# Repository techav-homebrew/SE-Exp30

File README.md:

# SE-Exp30 Mac SE Accelerator
Minimal 68030 &amp; 68882 accelerator card for the Macintosh SE

This project is not intended to be the fastest or most feature-rich accelerator for the Mac SE. Its primary goal is to be simple and transparent to Mac OS. Without the FPU, it should be able to function as just a faster Mac SE. To make full use of the FPU and the 68030's onboard cache, MacOS may need an init or extension to enable these features and advertise their presence to applications. 

The glue logic is entirely contained in a single 64-macrocel CPLD. Either an Altera EPM7064 or an Atmel ATF1504 will work. It is programmed and compiled for the Altera chip, but tested with the Atmel chip, using the free POF2JED software to convert the compiled configuration to the Atmel format. 

Should the initial design prove successful, future revisions may add cache or RAM on a 32-bit bus to further accelerate the SE. 

## Bill of Materials
Parts count is minimal
- Motorola 68030 CPU (MC68030RC or MC68030RP)
- Motorola 68882 FPU (MC68882RC)
- Microchip/Atmel ATF1504AS-10JU84 (PLLC-84)
- 7x 74'245 buffers (SOIC-20)
- 2x 10uF Electrolyic capacitors (5mm, 2.5mm lead spacing)
- 33x 1uF Ceramic capacitors (0805)
- 16x 4k7 resistors (0805)
- TTL Crystal Oscillator (DIP-8)
- DIN 41612-C 96-pin right-angle connector (male)
- optional 4-pin floppy/Berg power connector

None of the part values are especially critical. The oscillator frequency should match the intended CPU/FPU speed, and the speed grade for the CPLD should be appropriate for the target speed as well. Timing for the CPLD was planned with a 10ns CPLD and 50MHz CPU in mind. As the 68030 CPU and 68882 FPU are no longer produced, it is left to the reader to source these parts and determine the appropriate oscillator frequency to use with whatever parts are available. Processors were originally offered in 16MHz, 20MHz, 25MHz, 33MHz, 40MHz, and 50MHz ratings. It may be necessary to convert the PCB to 4-layers and insert internal power/ground planes to achieve higher clock rates. 

All capacitors on the BOM are included for bypass/filter purposes, so their values are not critical. Lower capacitance isn't recommended, but higher values may certainly be substituted. Similarly, the resistors only serve as pull-ups so their values are also not critical. 

## Power Supply
The Mac SE is rated to provide 7.5W on the 5V rail for PDS cards. This card may exceed that 7.5W rating. Depending on the configuration of the SE model (e.g. presence of a hard drive) and the health of the power supply, a separate 5V power supply may be necessary to power this accelerator. A footprint is provided for a 4-pin floppy (Berg) connector. If an external power supply is used, the jumpers J1, J2, J3 should be left open. If the card will be powered via the PDS slot, these jumpers should be closed, and nothing should be connected to the power connector.

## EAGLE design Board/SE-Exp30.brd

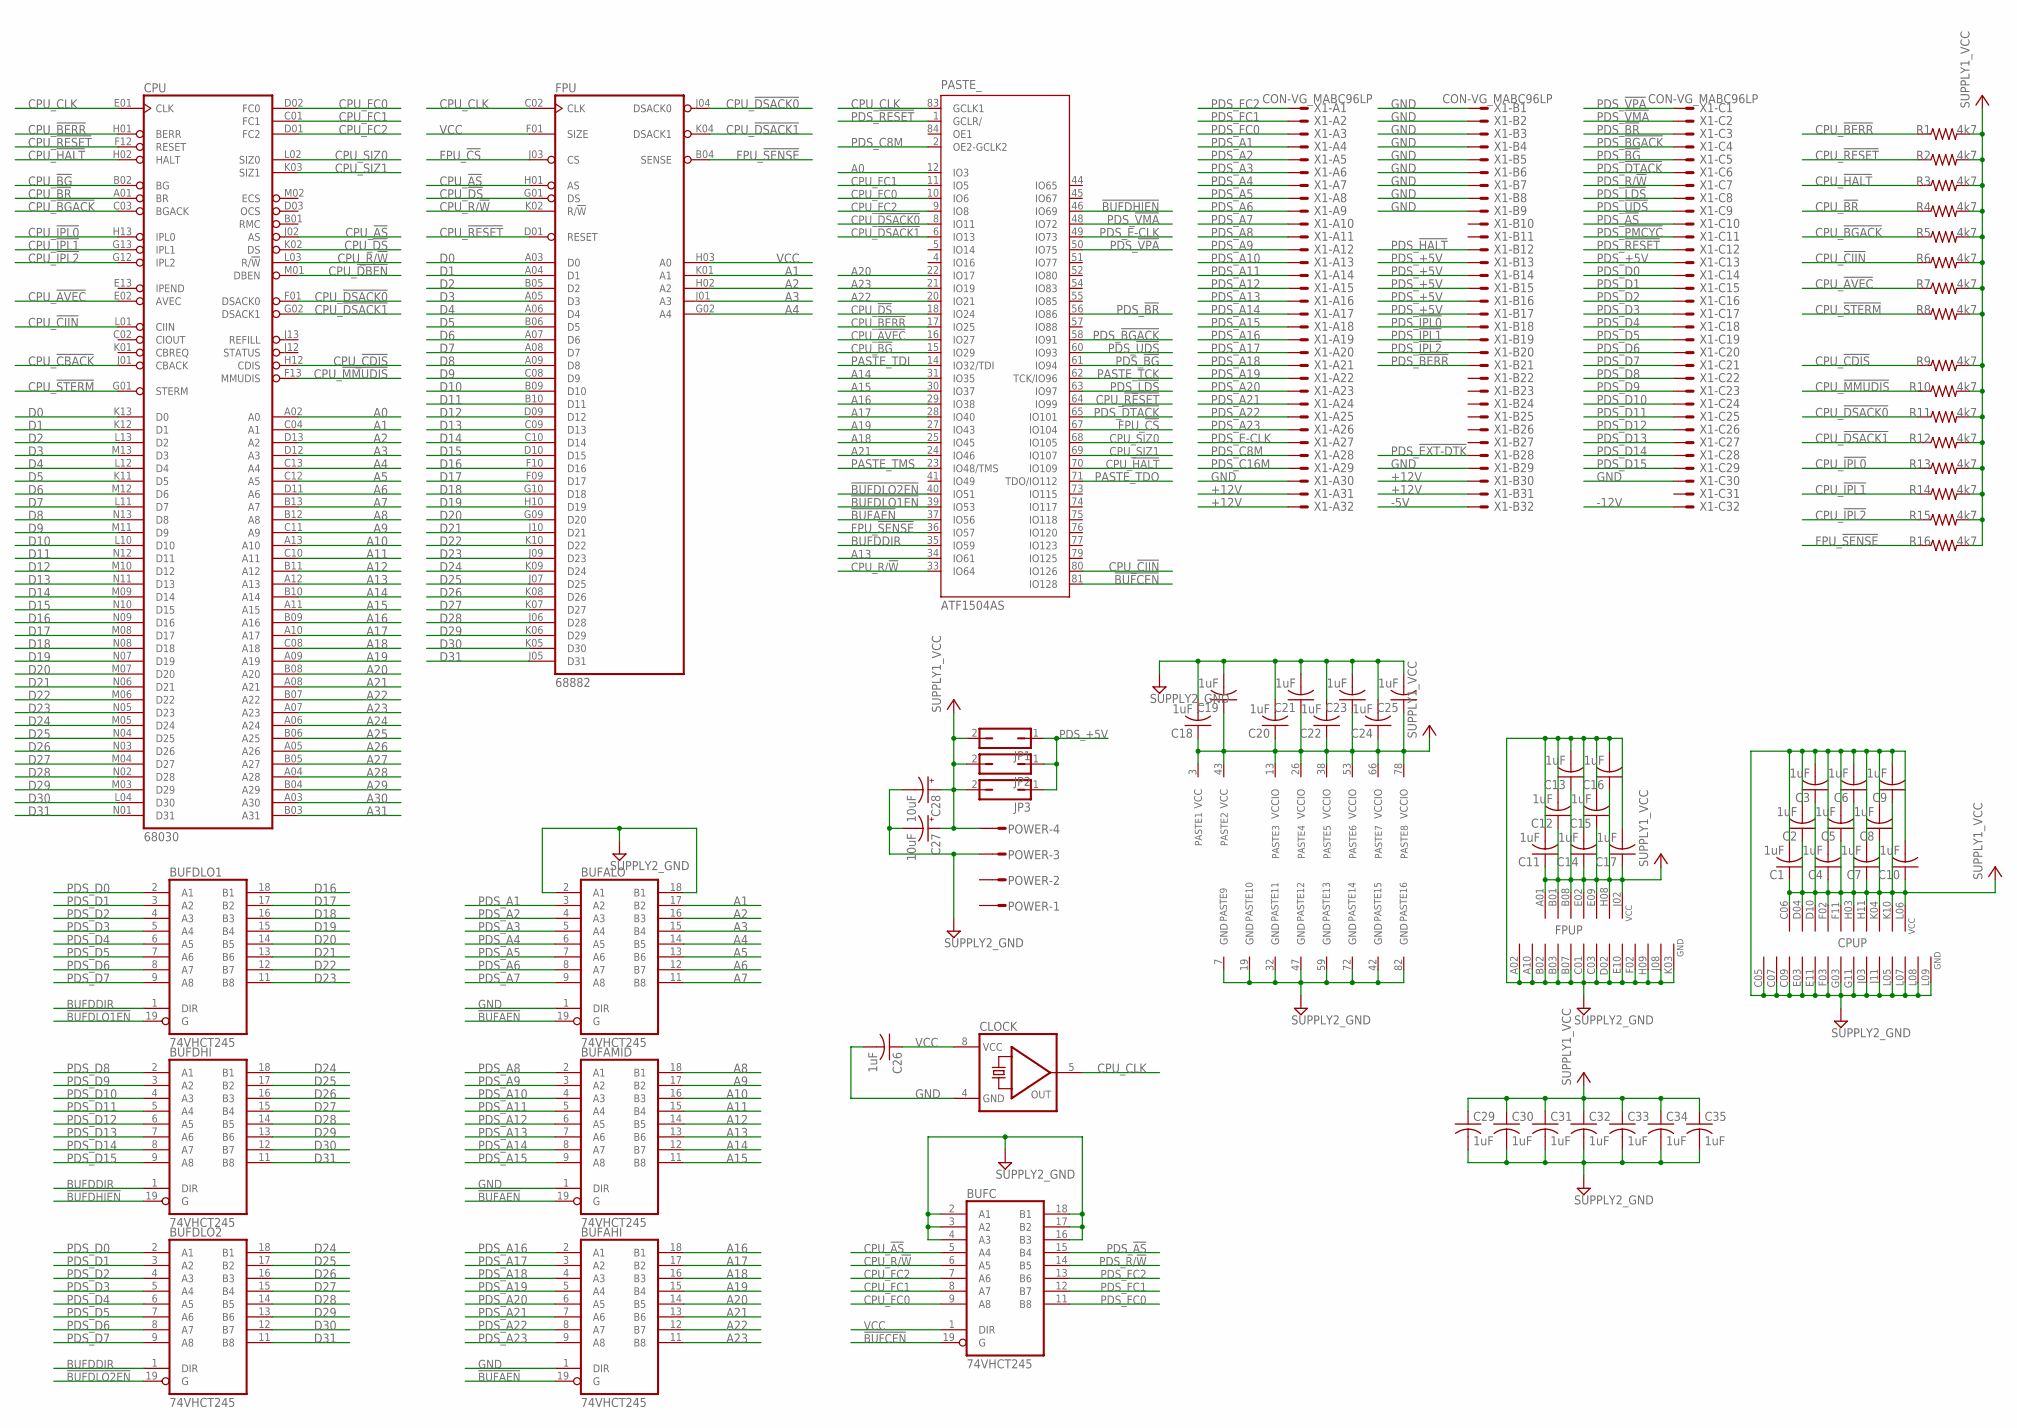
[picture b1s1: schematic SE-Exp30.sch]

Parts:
BUFAHI: 74VHCT245; 74XX-US_SO20W
BUFALO: 74VHCT245; 74XX-US_SO20W
BUFAMID: 74VHCT245; 74XX-US_SO20W
BUFC: 74VHCT245; 74XX-US_SO20W
BUFDHI: 74VHCT245; 74XX-US_SO20W
BUFDLO1, BUFDLO2: 74VHCT245; 74XX-US_SO20W
C1, C2, C3, C4, C5, C6, C7, C8, C9, C10, C11, C12, C13, C14, C15, C16, C17, C18, C19, C20, C21, C22, C23, C24, C25, C26, C29, C30, C31, C32, C33, C34, C35: 1uF; RCL_C0805
C27, C28: 10uF; RCL_E2,5-5
CLOCK: CRYSTAL_QG5460; CRYSTAL_DIL08S
CPU: 68030; MICRO-MC68000_MPGA128
FPU: 68882; MICRO-MC68000_MPGA68
JP1, JP2, JP3: JUMPER_JP1Q; JUMPER_JP1
PASTE: ATF1504AS; SE-EXP30_S84
POWER: CON-AMP-MT_L04P
R1, R2, R3, R4, R5, R6, R7, R8, R9, R10, R11, R12, R13, R14, R15, R16: 4k7; RCL_R0805
X1: CON-VG_MABC96LP

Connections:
!BUFAEN: BUFAHI.19 (G), BUFALO.19 (G), BUFAMID.19 (G), PASTE.37 (IO56)
!BUFCEN: BUFC.19 (G), PASTE.81 (IO128)
!BUFDHIEN: BUFDHI.19 (G), PASTE.46 (IO69)
!BUFDLO1EN: BUFDLO1.19 (G), PASTE.39 (IO53)
!BUFDLO2EN: BUFDLO2.19 (G), PASTE.40 (IO51)
+12V: X1.A31, X1.A32, X1.B30, X1.B31
-5V: X1.B32
-12V: X1.C32
A0: CPU.A02 (A0), PASTE.12 (IO3)
A1: BUFALO.17 (B2), CPU.C04 (A1), FPU.K01 (A1)
A2: BUFALO.16 (B3), CPU.D13 (A2), FPU.H02 (A2)
A3: BUFALO.15 (B4), CPU.D12 (A3), FPU.J01 (A3)
A4: BUFALO.14 (B5), CPU.C13 (A4), FPU.G02 (A4)
A5: BUFALO.13 (B6), CPU.C12 (A5)
A6: BUFALO.12 (B7), CPU.D11 (A6)
A7: BUFALO.11 (B8), CPU.B13 (A7)
A8: BUFAMID.18 (B1), CPU.B12 (A8)
A9: BUFAMID.17 (B2), CPU.C11 (A9)
A10: BUFAMID.16 (B3), CPU.A13 (A10)
A11: BUFAMID.15 (B4), CPU.C10 (A11)
A12: BUFAMID.14 (B5), CPU.B11 (A12)
A13: BUFAMID.13 (B6), CPU.A12 (A13), PASTE.34 (IO61)
A14: BUFAMID.12 (B7), CPU.B10 (A14), PASTE.31 (IO35)
A15: BUFAMID.11 (B8), CPU.A11 (A15), PASTE.30 (IO37)
A16: BUFAHI.18 (B1), CPU.B09 (A16), PASTE.29 (IO38)
A17: BUFAHI.17 (B2), CPU.A10 (A17), PASTE.28 (IO40)
A18: BUFAHI.16 (B3), CPU.C08 (A18), PASTE.25 (IO45)
A19: BUFAHI.15 (B4), CPU.A09 (A19), PASTE.27 (IO43)
A20: BUFAHI.14 (B5), CPU.B08 (A20), PASTE.22 (IO17)
A21: BUFAHI.13 (B6), CPU.A08 (A21), PASTE.24 (IO46)
A22: BUFAHI.12 (B7), CPU.B07 (A22), PASTE.20 (IO21)
A23: BUFAHI.11 (B8), CPU.A07 (A23), PASTE.21 (IO19)
A24: CPU.A06 (A24)
A25: CPU.B06 (A25)
A26: CPU.A05 (A26)
A27: CPU.B05 (A27)
A28: CPU.A04 (A28)
A29: CPU.B04 (A29)
A30: CPU.A03 (A30)
A31: CPU.B03 (A31)
BUFDDIR: BUFDHI.1 (DIR), BUFDLO1.1 (DIR), BUFDLO2.1 (DIR), PASTE.35 (IO59)
CPU_!AS: BUFC.5 (A4), CPU.J02 (AS), FPU.H01 (AS)
CPU_!AVEC: CPU.E02 (AVEC), PASTE.16 (IO27), R7.1
CPU_!BERR: CPU.H01 (BERR), PASTE.17 (IO25), R1.1
CPU_!BG: CPU.B02 (BG), PASTE.15 (IO29)
CPU_!BGACK: CPU.C03 (BGACK), R5.1
CPU_!BR: CPU.A01 (BR), R4.1
CPU_!CBACK: CPU.J01 (CBACK)
CPU_!CDIS: CPU.H12 (CDIS), R9.1
CPU_!CIIN: CPU.L01 (CIIN), PASTE.80 (IO126), R6.1
CPU_!DBEN: CPU.M01 (DBEN)
CPU_!DS: CPU.K02 (DS), FPU.G01 (DS), PASTE.18 (IO24)
CPU_!DSACK0: CPU.F01 (DSACK0), FPU.J04 (DSACK0), PASTE.8 (IO11), R11.1
CPU_!DSACK1: CPU.G02 (DSACK1), FPU.K04 (DSACK1), PASTE.6 (IO13), R12.1
CPU_!HALT: CPU.H02 (HALT), PASTE.70 (IO109), R3.1
CPU_!IPL0: CPU.H13 (IPL0), R13.1
CPU_!IPL1: CPU.G13 (IPL1), R14.1
CPU_!IPL2: CPU.G12 (IPL2), R15.1
CPU_!MMUDIS: CPU.F13 (MMUDIS), R10.1
CPU_!RESET: CPU.F12 (RESET), FPU.D01 (RESET), PASTE.64 (IO99), R2.1
CPU_!STERM: CPU.G01 (STERM), R8.1
CPU_CLK: CLOCK.5 (OUT), CPU.E01 (CLK), FPU.C02 (CLK), PASTE.83 (GCLK1)
CPU_FC0: BUFC.9 (A8), CPU.D02 (FC0), PASTE.10 (IO6)
CPU_FC1: BUFC.8 (A7), CPU.C01 (FC1), PASTE.11 (IO5)
CPU_FC2: BUFC.7 (A6), CPU.D01 (FC2), PASTE.9 (IO8)
CPU_R/!W: BUFC.6 (A5), CPU.L03 (R/!W), FPU.K02 (R/!W), PASTE.33 (IO64)
CPU_SIZ0: CPU.L02 (SIZ0), PASTE.68 (IO105)
CPU_SIZ1: CPU.K03 (SIZ1), PASTE.69 (IO107)
D0: CPU.K13 (D0), FPU.A03 (D0)
D1: CPU.K12 (D1), FPU.A04 (D1)
D2: CPU.L13 (D2), FPU.B05 (D2)
D3: CPU.M13 (D3), FPU.A05 (D3)
D4: CPU.L12 (D4), FPU.A06 (D4)
D5: CPU.K11 (D5), FPU.B06 (D5)
D6: CPU.M12 (D6), FPU.A07 (D6)
D7: CPU.L11 (D7), FPU.A08 (D7)
D8: CPU.N13 (D8), FPU.A09 (D8)
D9: CPU.M11 (D9), FPU.C08 (D9)
D10: CPU.L10 (D10), FPU.B09 (D10)
D11: CPU.N12 (D11), FPU.B10 (D11)
D12: CPU.M10 (D12), FPU.D09 (D12)
D13: CPU.N11 (D13), FPU.C09 (D13)
D14: CPU.M09 (D14), FPU.C10 (D14)
D15: CPU.N10 (D15), FPU.D10 (D15)
D16: BUFDLO1.18 (B1), CPU.N09 (D16), FPU.F10 (D16)
D17: BUFDLO1.17 (B2), CPU.M08 (D17), FPU.F09 (D17)
D18: BUFDLO1.16 (B3), CPU.N08 (D18), FPU.G10 (D18)
D19: BUFDLO1.15 (B4), CPU.N07 (D19), FPU.H10 (D19)
D20: BUFDLO1.14 (B5), CPU.M07 (D20), FPU.G09 (D20)
D21: BUFDLO1.13 (B6), CPU.N06 (D21), FPU.J10 (D21)
D22: BUFDLO1.12 (B7), CPU.M06 (D22), FPU.K10 (D22)
D23: BUFDLO1.11 (B8), CPU.N05 (D23), FPU.J09 (D23)
D24: BUFDHI.18 (B1), BUFDLO2.18 (B1), CPU.M05 (D24), FPU.K09 (D24)
D25: BUFDHI.17 (B2), BUFDLO2.17 (B2), CPU.N04 (D25), FPU.J07 (D25)
D26: BUFDHI.16 (B3), BUFDLO2.16 (B3), CPU.N03 (D26), FPU.K08 (D26)
D27: BUFDHI.15 (B4), BUFDLO2.15 (B4), CPU.M04 (D27), FPU.K07 (D27)
D28: BUFDHI.14 (B5), BUFDLO2.14 (B5), CPU.N02 (D28), FPU.J06 (D28)
D29: BUFDHI.13 (B6), BUFDLO2.13 (B6), CPU.M03 (D29), FPU.K06 (D29)
D30: BUFDHI.12 (B7), BUFDLO2.12 (B7), CPU.L04 (D30), FPU.K05 (D30)
D31: BUFDHI.11 (B8), BUFDLO2.11 (B8), CPU.N01 (D31), FPU.J05 (D31)
FPU_!CS: FPU.J03 (CS), PASTE.67 (IO104)
FPU_!SENSE: FPU.B04 (SENSE), PASTE.36 (IO57), R16.1
GND: BUFAHI.1 (DIR), BUFAHI.10 (GND), BUFALO.1 (DIR), BUFALO.2 (A1), BUFALO.10 (GND), BUFALO.18 (B1), BUFAMID.1 (DIR), BUFAMID.10 (GND), BUFC.2 (A1), BUFC.3 (A2), BUFC.4 (A3), BUFC.10 (GND), BUFC.16 (B3), BUFC.17 (B2), BUFC.18 (B1), BUFDHI.10 (GND), BUFDLO1.10 (GND), BUFDLO2.10 (GND), C1.2, C2.2, C3.2, C4.2, C5.2, C6.2, C7.2, C8.2, C9.2, C10.2, C11.2, C12.2, C13.2, C14.2, C15.2, C16.2, C17.2, C18.2, C19.2, C20.2, C21.2, C22.2, C23.2, C24.2, C25.2, C26.2, C27.-, C28.-, C29.2, C30.2, C31.2, C32.2, C33.2, C34.2, C35.2, CLOCK.4 (GND), CPU.C05 (GND), CPU.C07 (GND), CPU.C09 (GND), CPU.E03 (GND), CPU.E11 (GND), CPU.F03 (GND), CPU.G03 (GND), CPU.G11 (GND), CPU.J03 (GND), CPU.J11 (GND), CPU.L05 (GND), CPU.L07 (GND), CPU.L08 (GND), CPU.L09 (GND), FPU.A02 (GND), FPU.A10 (GND), FPU.B02 (GND), FPU.B03 (GND), FPU.B07 (GND), FPU.C01 (GND), FPU.C03 (GND), FPU.D02 (GND), FPU.E10 (GND), FPU.F02 (GND), FPU.H09 (GND), FPU.J08 (GND), FPU.K03 (GND), PASTE.7 (GND), PASTE.19 (GND), PASTE.32 (GND), PASTE.42 (GND), PASTE.47 (GND), PASTE.59 (GND), PASTE.72 (GND), PASTE.82 (GND), POWER.3, X1.A30, X1.B1, X1.B2, X1.B3, X1.B4, X1.B5, X1.B6, X1.B7, X1.B8, X1.B9, X1.B29, X1.C30
PASTE_TCK: PASTE.62 (TCK/IO96)
PASTE_TDI: PASTE.14 (IO32/TDI)
PASTE_TDO: PASTE.71 (TDO/IO112)
PASTE_TMS: PASTE.23 (IO48/TMS)
PDS_!AS: BUFC.15 (B4), X1.C10
PDS_!BERR: X1.B21
PDS_!BG: PASTE.61 (IO94), X1.C5
PDS_!BGACK: PASTE.58 (IO91), X1.C4
PDS_!BR: PASTE.56 (IO86), X1.C3
PDS_!DTACK: PASTE.65 (IO101), X1.C6
PDS_!EXT-DTK: X1.B28
PDS_!HALT: X1.B12
PDS_!IPL0: X1.B18
PDS_!IPL1: X1.B19
PDS_!IPL2: X1.B20
PDS_!LDS: PASTE.63 (IO97), X1.C8
PDS_!PMCYC: X1.C11
PDS_!RESET: PASTE.1 (GCLR/), X1.C12
PDS_!UDS: PASTE.60 (IO93), X1.C9
PDS_!VMA: PASTE.48 (IO72), X1.C2
PDS_!VPA: PASTE.50 (IO75), X1.C1
PDS_+5V: JP1.1, JP2.1, JP3.1, X1.B13, X1.B14, X1.B15, X1.B16, X1.B17, X1.C13
PDS_A1: BUFALO.3 (A2), X1.A4
PDS_A2: BUFALO.4 (A3), X1.A5
PDS_A3: BUFALO.5 (A4), X1.A6
PDS_A4: BUFALO.6 (A5), X1.A7
PDS_A5: BUFALO.7 (A6), X1.A8
PDS_A6: BUFALO.8 (A7), X1.A9
PDS_A7: BUFALO.9 (A8), X1.A10
PDS_A8: BUFAMID.2 (A1), X1.A11
PDS_A9: BUFAMID.3 (A2), X1.A12
PDS_A10: BUFAMID.4 (A3), X1.A13
PDS_A11: BUFAMID.5 (A4), X1.A14
PDS_A12: BUFAMID.6 (A5), X1.A15
PDS_A13: BUFAMID.7 (A6), X1.A16
PDS_A14: BUFAMID.8 (A7), X1.A17
PDS_A15: BUFAMID.9 (A8), X1.A18
PDS_A16: BUFAHI.2 (A1), X1.A19
PDS_A17: BUFAHI.3 (A2), X1.A20
PDS_A18: BUFAHI.4 (A3), X1.A21
PDS_A19: BUFAHI.5 (A4), X1.A22
PDS_A20: BUFAHI.6 (A5), X1.A23
PDS_A21: BUFAHI.7 (A6), X1.A24
PDS_A22: BUFAHI.8 (A7), X1.A25
PDS_A23: BUFAHI.9 (A8), X1.A26
PDS_C8M: PASTE.2 (OE2-GCLK2), X1.A28
PDS_C16M: X1.A29
PDS_D0: BUFDLO1.2 (A1), BUFDLO2.2 (A1), X1.C14
PDS_D1: BUFDLO1.3 (A2), BUFDLO2.3 (A2), X1.C15
PDS_D2: BUFDLO1.4 (A3), BUFDLO2.4 (A3), X1.C16
PDS_D3: BUFDLO1.5 (A4), BUFDLO2.5 (A4), X1.C17
PDS_D4: BUFDLO1.6 (A5), BUFDLO2.6 (A5), X1.C18
PDS_D5: BUFDLO1.7 (A6), BUFDLO2.7 (A6), X1.C19
PDS_D6: BUFDLO1.8 (A7), BUFDLO2.8 (A7), X1.C20
PDS_D7: BUFDLO1.9 (A8), BUFDLO2.9 (A8), X1.C21
PDS_D8: BUFDHI.2 (A1), X1.C22
PDS_D9: BUFDHI.3 (A2), X1.C23
PDS_D10: BUFDHI.4 (A3), X1.C24
PDS_D11: BUFDHI.5 (A4), X1.C25
PDS_D12: BUFDHI.6 (A5), X1.C26
PDS_D13: BUFDHI.7 (A6), X1.C27
PDS_D14: BUFDHI.8 (A7), X1.C28
PDS_D15: BUFDHI.9 (A8), X1.C29
PDS_E-CLK: PASTE.49 (IO73), X1.A27
PDS_FC0: BUFC.11 (B8), X1.A3
PDS_FC1: BUFC.12 (B7), X1.A2
PDS_FC2: BUFC.13 (B6), X1.A1
PDS_R/!W: BUFC.14 (B5), X1.C7
VCC: BUFAHI.20 (VCC), BUFALO.20 (VCC), BUFAMID.20 (VCC), BUFC.1 (DIR), BUFC.20 (VCC), BUFDHI.20 (VCC), BUFDLO1.20 (VCC), BUFDLO2.20 (VCC), C1.1, C2.1, C3.1, C4.1, C5.1, C6.1, C7.1, C8.1, C9.1, C10.1, C11.1, C12.1, C13.1, C14.1, C15.1, C16.1, C17.1, C18.1, C19.1, C20.1, C21.1, C22.1, C23.1, C24.1, C25.1, C26.1, C27.+, C28.+, C29.1, C30.1, C31.1, C32.1, C33.1, C34.1, C35.1, CLOCK.8 (VCC), CPU.C06 (VCC), CPU.D04 (VCC), CPU.D10 (VCC), CPU.F02 (VCC), CPU.F11 (VCC), CPU.H03 (VCC), CPU.H11 (VCC), CPU.K04 (VCC), CPU.K10 (VCC), CPU.L06 (VCC), FPU.A01 (VCC), FPU.B01 (VCC), FPU.B08 (VCC), FPU.E02 (VCC), FPU.E09 (VCC), FPU.F01 (SIZE), FPU.H03 (A0), FPU.H08 (VCC), FPU.J02 (VCC), JP1.2, JP2.2, JP3.2, PASTE.3 (VCC), PASTE.13 (VCCIO), PASTE.26 (VCCIO), PASTE.38 (VCCIO), PASTE.43 (VCC), PASTE.53 (VCCIO), PASTE.66 (VCCIO), PASTE.78 (VCCIO), POWER.4, R1.2, R2.2, R3.2, R4.2, R5.2, R6.2, R7.2, R8.2, R9.2, R10.2, R11.2, R12.2, R13.2, R14.2, R15.2, R16.2

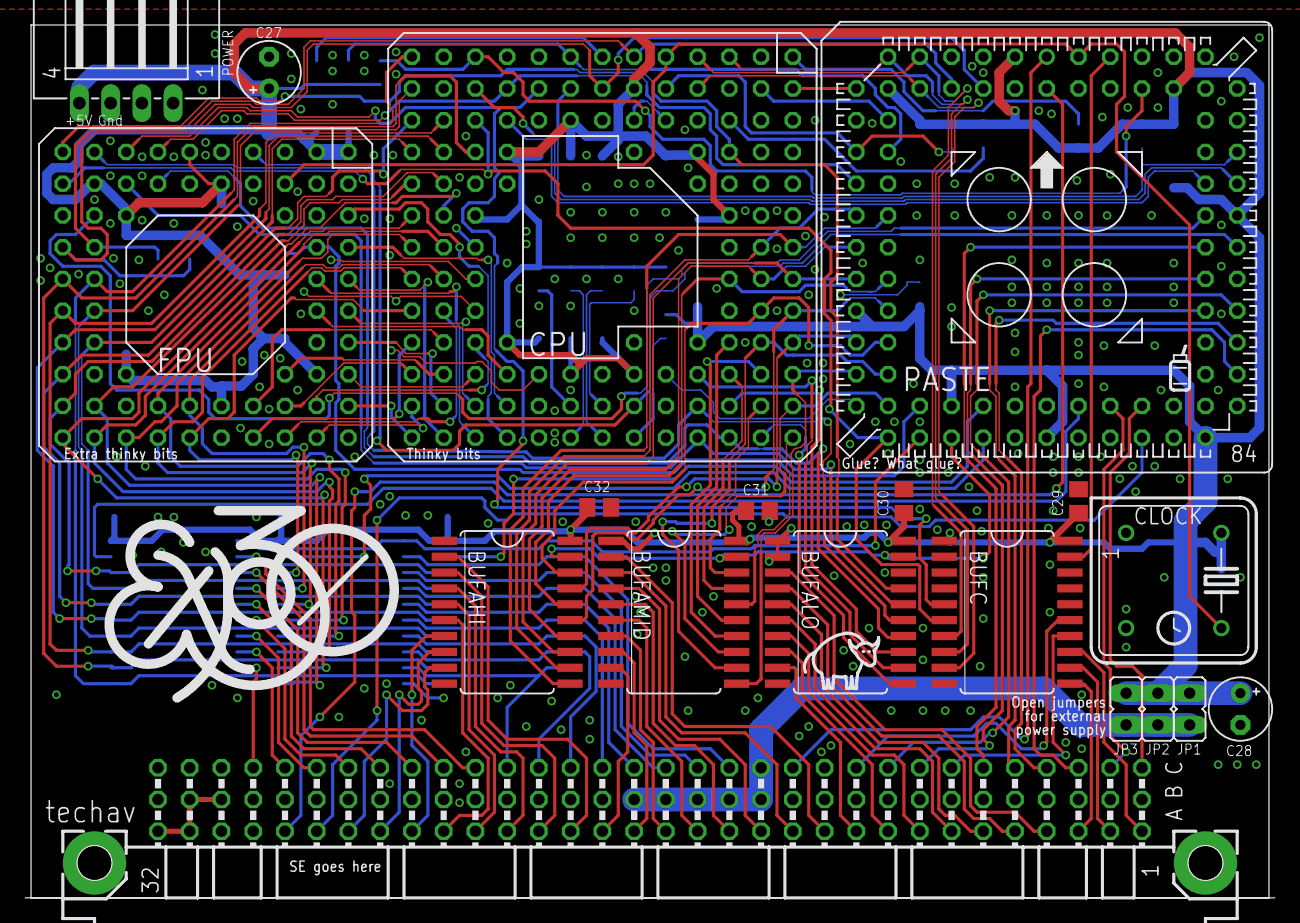
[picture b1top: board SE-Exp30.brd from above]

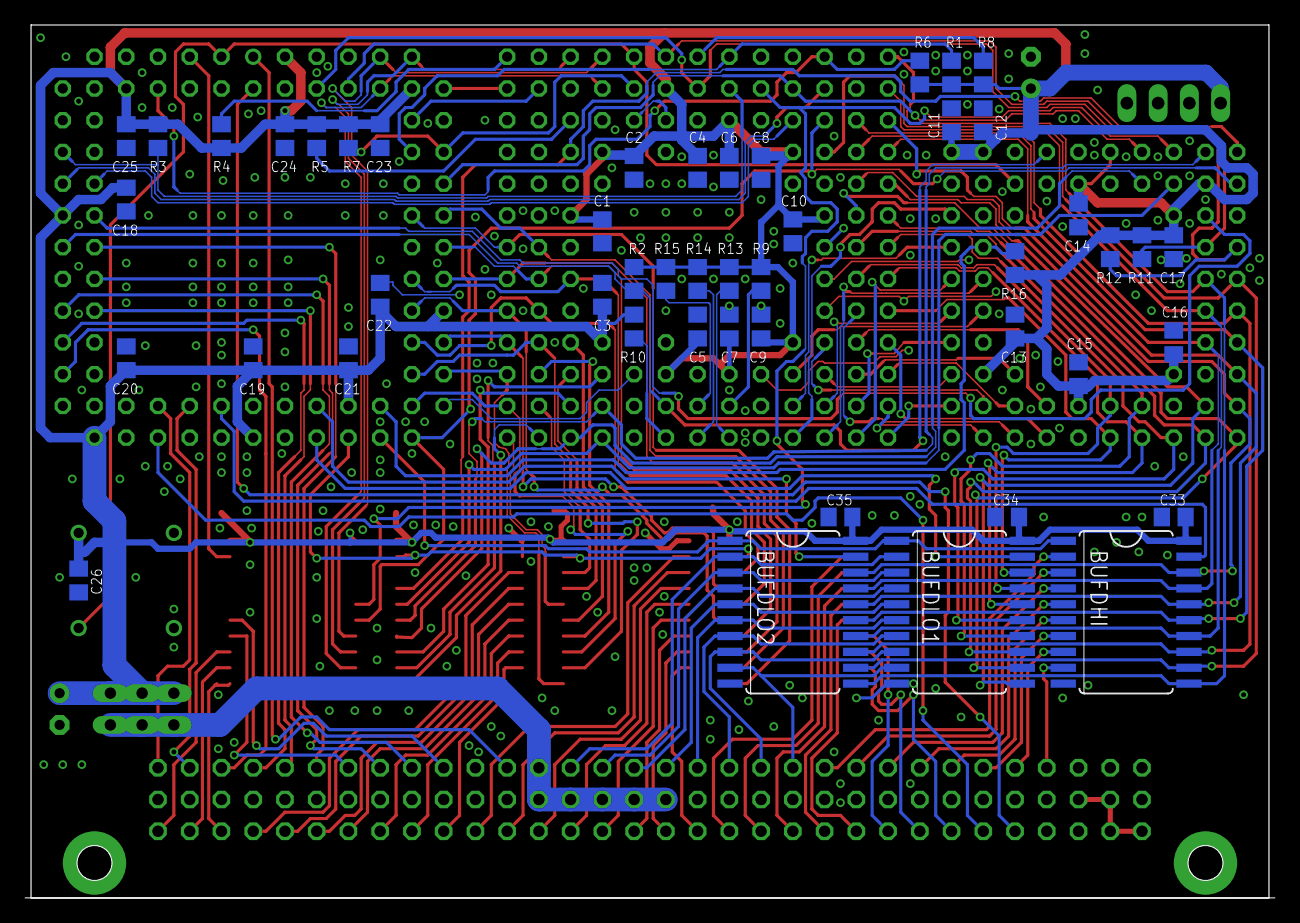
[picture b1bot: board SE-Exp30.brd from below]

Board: 2 copper layers, 99.1 x 69.8 mm, 68 parts (48 on the bottom side), 148 nets.

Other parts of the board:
U$1: BUFFALO

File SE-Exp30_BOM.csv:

Part,Value,Device,Package,Description,Mfg,Mfg Part,Mouser Part
BUFAHI,74VHCT245,74LS245DW,SO20W,"Octal BUS TRANSCEIVER, 3-state",Toshiba,74VHCT245AFT(BE),757-74VHCT245AFTBE
BUFALO,74VHCT245,74LS245DW,SO20W,"Octal BUS TRANSCEIVER, 3-state",Toshiba,74VHCT245AFT(BE),757-74VHCT245AFTBE
BUFAMID,74VHCT245,74LS245DW,SO20W,"Octal BUS TRANSCEIVER, 3-state",Toshiba,74VHCT245AFT(BE),757-74VHCT245AFTBE
BUFC,74VHCT245,74LS245DW,SO20W,"Octal BUS TRANSCEIVER, 3-state",Toshiba,74VHCT245AFT(BE),757-74VHCT245AFTBE
BUFDHI,74VHCT245,74LS245DW,SO20W,"Octal BUS TRANSCEIVER, 3-state",Toshiba,74VHCT245AFT(BE),757-74VHCT245AFTBE
BUFDLO1,74VHCT245,74LS245DW,SO20W,"Octal BUS TRANSCEIVER, 3-state",Toshiba,74VHCT245AFT(BE),757-74VHCT245AFTBE
BUFDLO2,74VHCT245,74LS245DW,SO20W,"Octal BUS TRANSCEIVER, 3-state",Toshiba,74VHCT245AFT(BE),757-74VHCT245AFTBE
C1,1uF,C-USC0805,C0805,"CAPACITOR, American symbol",Kemet,C0805C105Z4VACTU,80-C0805C105Z4V
C2,1uF,C-USC0805,C0805,"CAPACITOR, American symbol",Kemet,C0805C105Z4VACTU,80-C0805C105Z4V
C3,1uF,C-USC0805,C0805,"CAPACITOR, American symbol",Kemet,C0805C105Z4VACTU,80-C0805C105Z4V
C4,1uF,C-USC0805,C0805,"CAPACITOR, American symbol",Kemet,C0805C105Z4VACTU,80-C0805C105Z4V
C5,1uF,C-USC0805,C0805,"CAPACITOR, American symbol",Kemet,C0805C105Z4VACTU,80-C0805C105Z4V
C6,1uF,C-USC0805,C0805,"CAPACITOR, American symbol",Kemet,C0805C105Z4VACTU,80-C0805C105Z4V
C7,1uF,C-USC0805,C0805,"CAPACITOR, American symbol",Kemet,C0805C105Z4VACTU,80-C0805C105Z4V
C8,1uF,C-USC0805,C0805,"CAPACITOR, American symbol",Kemet,C0805C105Z4VACTU,80-C0805C105Z4V
C9,1uF,C-USC0805,C0805,"CAPACITOR, American symbol",Kemet,C0805C105Z4VACTU,80-C0805C105Z4V
C10,1uF,C-USC0805,C0805,"CAPACITOR, American symbol",Kemet,C0805C105Z4VACTU,80-C0805C105Z4V
C11,1uF,C-USC0805,C0805,"CAPACITOR, American symbol",Kemet,C0805C105Z4VACTU,80-C0805C105Z4V
C12,1uF,C-USC0805,C0805,"CAPACITOR, American symbol",Kemet,C0805C105Z4VACTU,80-C0805C105Z4V
C13,1uF,C-USC0805,C0805,"CAPACITOR, American symbol",Kemet,C0805C105Z4VACTU,80-C0805C105Z4V
C14,1uF,C-USC0805,C0805,"CAPACITOR, American symbol",Kemet,C0805C105Z4VACTU,80-C0805C105Z4V
C15,1uF,C-USC0805,C0805,"CAPACITOR, American symbol",Kemet,C0805C105Z4VACTU,80-C0805C105Z4V
C16,1uF,C-USC0805,C0805,"CAPACITOR, American symbol",Kemet,C0805C105Z4VACTU,80-C0805C105Z4V
C17,1uF,C-USC0805,C0805,"CAPACITOR, American symbol",Kemet,C0805C105Z4VACTU,80-C0805C105Z4V
C18,1uF,C-USC0805,C0805,"CAPACITOR, American symbol",Kemet,C0805C105Z4VACTU,80-C0805C105Z4V
C19,1uF,C-USC0805,C0805,"CAPACITOR, American symbol",Kemet,C0805C105Z4VACTU,80-C0805C105Z4V
C20,1uF,C-USC0805,C0805,"CAPACITOR, American symbol",Kemet,C0805C105Z4VACTU,80-C0805C105Z4V
C21,1uF,C-USC0805,C0805,"CAPACITOR, American symbol",Kemet,C0805C105Z4VACTU,80-C0805C105Z4V
C22,1uF,C-USC0805,C0805,"CAPACITOR, American symbol",Kemet,C0805C105Z4VACTU,80-C0805C105Z4V
C23,1uF,C-USC0805,C0805,"CAPACITOR, American symbol",Kemet,C0805C105Z4VACTU,80-C0805C105Z4V
C24,1uF,C-USC0805,C0805,"CAPACITOR, American symbol",Kemet,C0805C105Z4VACTU,80-C0805C105Z4V
C25,1uF,C-USC0805,C0805,"CAPACITOR, American symbol",Kemet,C0805C105Z4VACTU,80-C0805C105Z4V
C26,1uF,C-USC0805,C0805,"CAPACITOR, American symbol",Kemet,C0805C105Z4VACTU,80-C0805C105Z4V
C27,10uF,CPOL-USE2.5-5,"E2,5-5","POLARIZED CAPACITOR, American symbol",Panasonic,ECA-1EM100I,667-ECA-1EM100I
C28,10uF,CPOL-USE2.5-5,"E2,5-5","POLARIZED CAPACITOR, American symbol",Panasonic,ECA-1EM100I,667-ECA-1EM100I
C29,1uF,C-USC0805,C0805,"CAPACITOR, American symbol",Kemet,C0805C105Z4VACTU,80-C0805C105Z4V
C30,1uF,C-USC0805,C0805,"CAPACITOR, American symbol",Kemet,C0805C105Z4VACTU,80-C0805C105Z4V
C31,1uF,C-USC0805,C0805,"CAPACITOR, American symbol",Kemet,C0805C105Z4VACTU,80-C0805C105Z4V
C32,1uF,C-USC0805,C0805,"CAPACITOR, American symbol",Kemet,C0805C105Z4VACTU,80-C0805C105Z4V
C33,1uF,C-USC0805,C0805,"CAPACITOR, American symbol",Kemet,C0805C105Z4VACTU,80-C0805C105Z4V
C34,1uF,C-USC0805,C0805,"CAPACITOR, American symbol",Kemet,C0805C105Z4VACTU,80-C0805C105Z4V
C35,1uF,C-USC0805,C0805,"CAPACITOR, American symbol",Kemet,C0805C105Z4VACTU,80-C0805C105Z4V
CLOCK,,QG5460,DIL08S,CRYSTAL RESONATOR,,,
CPU,68030,MC68030RC,MPGA128,68xxx PROCESSOR,Motorola,MC68030RCxx,
FPU,68882,MC68881RC,MPGA68,68xxx PROCESSOR,Motorola,MC68882RCxx,
JP1,,JP1Q,JP1,JUMPER,,,
JP2,,JP1Q,JP1,JUMPER,,,
JP3,,JP1Q,JP1,JUMPER,,,
PASTE,ATF1504AS,EPM7128-J84S,S84,EPM70128,Microchip,ATF1504AS-10JU84,556-AF1504AS10JU84
POWER,,L04P,L04P,AMP MT CONNECTOR,TE Connectivity,171826-4,571-1718264
R1,4k7,R-US_R0805,R0805,"RESISTOR, American symbol",Vishay,CRCW08054K70JNEAC,71-CRCW08054K70JNEAC
R2,4k7,R-US_R0805,R0805,"RESISTOR, American symbol",Vishay,CRCW08054K70JNEAC,71-CRCW08054K70JNEAC
R3,4k7,R-US_R0805,R0805,"RESISTOR, American symbol",Vishay,CRCW08054K70JNEAC,71-CRCW08054K70JNEAC
R4,4k7,R-US_R0805,R0805,"RESISTOR, American symbol",Vishay,CRCW08054K70JNEAC,71-CRCW08054K70JNEAC
R5,4k7,R-US_R0805,R0805,"RESISTOR, American symbol",Vishay,CRCW08054K70JNEAC,71-CRCW08054K70JNEAC
R6,4k7,R-US_R0805,R0805,"RESISTOR, American symbol",Vishay,CRCW08054K70JNEAC,71-CRCW08054K70JNEAC
R7,4k7,R-US_R0805,R0805,"RESISTOR, American symbol",Vishay,CRCW08054K70JNEAC,71-CRCW08054K70JNEAC
R8,4k7,R-US_R0805,R0805,"RESISTOR, American symbol",Vishay,CRCW08054K70JNEAC,71-CRCW08054K70JNEAC
R9,4k7,R-US_R0805,R0805,"RESISTOR, American symbol",Vishay,CRCW08054K70JNEAC,71-CRCW08054K70JNEAC
R10,4k7,R-US_R0805,R0805,"RESISTOR, American symbol",Vishay,CRCW08054K70JNEAC,71-CRCW08054K70JNEAC
R11,4k7,R-US_R0805,R0805,"RESISTOR, American symbol",Vishay,CRCW08054K70JNEAC,71-CRCW08054K70JNEAC
R12,4k7,R-US_R0805,R0805,"RESISTOR, American symbol",Vishay,CRCW08054K70JNEAC,71-CRCW08054K70JNEAC
R13,4k7,R-US_R0805,R0805,"RESISTOR, American symbol",Vishay,CRCW08054K70JNEAC,71-CRCW08054K70JNEAC
R14,4k7,R-US_R0805,R0805,"RESISTOR, American symbol",Vishay,CRCW08054K70JNEAC,71-CRCW08054K70JNEAC
R15,4k7,R-US_R0805,R0805,"RESISTOR, American symbol",Vishay,CRCW08054K70JNEAC,71-CRCW08054K70JNEAC
R16,4k7,R-US_R0805,R0805,"RESISTOR, American symbol",Vishay,CRCW08054K70JNEAC,71-CRCW08054K70JNEAC
X1,MABC96LP,MABC96LP,MABC96LP,"CONNECTOR male, 96 pins, type C, rows ABC, grid 2.54 mm with mounting clip",TE Connectivity,650473-5 ,571-6504735

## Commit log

2021-03-21 First draft PASTE logic
2021-03-22 Syntax fixes, added CIIN
2021-03-22 CIIN fix
2021-03-25 Initial BOM
2021-03-25 Readme
2021-03-25 Initial schematic and board
2021-03-25 Add Schematic pdf
2021-07-04 Debug1
2021-07-04 New Synchronous Logic
2021-07-04 BOM Correction
2021-09-28 Rewrite First Draft
2021-10-03 Bus Synchronization Fixes
